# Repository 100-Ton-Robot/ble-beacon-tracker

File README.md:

# BLE Beacon Tracker (DIY)

A passive BLE beacon locator. Three Seeed XIAO nRF54L15 scanners sit behind directional antennas
facing out 120 deg apart. Comparing RSSI between sectors gives a bearing, and RSSI gives a rough
range. An ESP32-S3 Ethernet gateway (ESPHome) collects the scanners' data and publishes it to MQTT
for a tracker in Home Assistant.

Passive RSSI only: it works with any beacon, with no pairing and no Channel Sounding.

## What's here

| Folder | What it is |
| --- | --- |
| [`scanner_fw/`](scanner_fw/README.md) | Scanner firmware: nRF Connect SDK / Zephyr behind MCUboot, with signed BLE updates. Build, flash, console commands; gateway protocol in `scanner_fw/PROTOCOL.md`. |
| [`gateway/`](gateway/README.md) | ESPHome package, per-mast example config and the `sector_scanner` external component: protocol 3 buckets in, MQTT layout v3 out (batched RSSI, Theengs-style adverts, status, events, security stream, retained scanner state); the RX pin is the sector; watches each sector's chip ID, checks each scanner's firmware version and its input, drops the mast's ignore list, keeps the scanners' settings applied and passes commands to them. |
| `builds/` | The mast's shield deck, faces and end plate, two ways: the PCB build ([`builds/pcb/`](builds/pcb/README.md): Gerbers and a 1:1 print; build guide [`BUILD.md`](builds/pcb/BUILD.md)) and the hand build ([`builds/hand/`](builds/hand/README.md): printable 1:1 templates; build guide [`BUILD.md`](builds/hand/BUILD.md)). Each has its own `parameters.csv`. |
| [`boards/`](boards/README.md) | Module boards either build can use: the one-radio carrier (Up + two branch ports), a three-radio board and the LED add-on board (not designed in the repo yet), plus `lib/kicad_lib.py`, the KiCad helpers every board generator shares. |
| [`common/`](common/) | What both builds share: `parameters.csv` (faces and core, duck spacing, pipe, radio positions, enclosure, RF), `params.py` (loads common + one build's file) and `layout.py` (the derived layout both builds and the RF model use). |
| [`sim/`](sim/README.md) | ngspice models of the unified power + LED board (5 V rail, level-shifted data, boot pull-down, strip short) and a model of the LED direction ring. Values from `parameters.csv` files. |
| [`rf_model/`](rf_model/README.md) | openEMS (FDTD) model of one sector: deck, core and whips from the `parameters.csv` files (`--build pcb` or `hand`); gives the antenna pattern, match and isolation between sectors. Runs in Docker. |
| [`docs/ANTENNA_SELECTION.md`](docs/ANTENNA_SELECTION.md) | Which antenna and duck spacing to use, with the formulas and the RF results behind it. Generated by `docs/make_antenna_doc.py` from `parameters.csv` and the RF runs. |
| [`experiments/`](experiments/kicad_deck/README.md) | Side experiments (the deck redone in KiCad). |

Changes are listed in [`CHANGELOG.md`](CHANGELOG.md). How to report a vulnerability, and the
known security gaps that were reviewed and accepted (with the reasons), are in
[`SECURITY.md`](SECURITY.md). Prebuilt scanner update images are in
`scanner_fw/release/`. They only install on scanners whose
MCUboot was built with the same signing key, so build your own from source with your own key
(see `scanner_fw/README.md`).

## Status

Work in progress:
- Scanner firmware 0.7.0 (protocol 3) runs on three boards, checked over the USB console.
  0.8.0 (gateway TX moved from D6 to D8) is built but won't be flashed: D8 has no UART on the
  nRF54L15, so it can't carry the stream. Both builds are now drawn for relay protocol 4 star
  wiring (D10 uplink, D7 command RX, head D0 / D1 branch RX; see
  [Firmware and pins](builds/hand/README.md#firmware-and-pins-both-builds)). That firmware isn't written yet.
- The gateway (protocol 3, needs scanner firmware 0.5.0 or later) passes its boot self-test on
  a board, but hasn't received scanner data on real wiring yet.
- The Home Assistant tracker isn't written yet.

## Bugs and contributions

Bug reports and pull requests are welcome: use [Issues](../../issues). For firmware problems,
include the version, the console's `status` output and what you expected to happen.

## License

[MIT](LICENSE).

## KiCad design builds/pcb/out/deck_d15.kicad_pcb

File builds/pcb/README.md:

# Deck, face and end plate PCBs (parts on the deck)

The PCB build. The hand build of the same mast is in [`../hand/README.md`](../hand/README.md); both share [`common/parameters.csv`](../../common/parameters.csv) and [`common/layout.py`](../../common/layout.py). This build's own numbers (tracks, clearances, part positions, face tabs, end plate) are in [`parameters.csv`](parameters.csv) here.

Five boards, generated with KiCad from [`make_pcbs.py`](make_pcbs.py): two deck sizes (one per duck spacing), the face, the corner gusset and the optional end plate. **To build one, follow [`BUILD.md`](BUILD.md)**: decisions, boards to order with fab settings, BOM, the 1:1 print check and the assembly steps (generated from the CSVs here by `docs/make_build_docs.py`). This README describes the boards and how to regenerate them.

This build replaces the hand-drilled acrylic electronics plate, the bus board / unified stripboard and the hand-cut copper-clad faces. The older deck (`../hand/shield_deck_gerbers.zip`, 146 mm, no parts) and the plate templates stay in [`../hand/`](../hand/README.md) for the older build. Status: **generated and DRC-clean, not yet ordered or built** (revision 3, 2026-11-23; spec [`REV3_PLAN.md`](REV3_PLAN.md)). Preview: [`pcb_preview.png`](pcb_preview.png).

> **Unplug PoE before plugging in USB.** All modules share one 5 V rail, with no diodes. Plugging a USB cable into a XIAO or the ESP32 while the PoE splitter is feeding the deck ties the computer's USB VBUS to the splitter's 5 V. Power from PoE OR from USB, never both. Damage to the boards, the splitter or the computer from ignoring this is not covered by anything in this repo; you build and power it at your own risk. The same warning is on the deck, on each face and on the end plate, and "UNPLUG POE / BEFORE USB" sits right in front of each XIAO's USB-C plug (across the plug path) and beside J2 (both sides). Every warning has a drawn caution sign (triangle with !, ISO 7010 W001 style; the silkscreen font has no emoji).

> **Firmware:** this deck wires the radios for relay protocol 4 (star wiring: D10 uplink TX, D0 / D1 branch RX, D7 command RX). That firmware is not written yet; scanner firmware 0.8.0 and older (one TX per radio straight to the gateway) does not work on this deck. See [Firmware and pins](#firmware-and-pins-both-builds).

## Firmware and pins (both builds)

Both builds run the same scanner firmware ([`scanner_fw/`](../../scanner_fw/README.md)), but today the pins don't agree:

| | Uplink TX (to the gateway or the head radio) | Command RX | Branch RX |
| --- | --- | --- | --- |
| Hand build, templates page 6 (2026-11-24, relay protocol 4) | D10 (head S0 to the ESP32, S1 / S2 to the head) | D7 | head D0 (S1) / D1 (S2) |
| Hand build, masts wired before 2026-11-24 | D6 (issue #1's move to D8 is cancelled) | D7 | - |
| Scanner firmware 0.8.0 (`scanner_fw/app.overlay`) | D8 | D7 | - |
| PCB deck rev 3 (relay protocol 4) | D10 (head to J1 DATA, the other two to the head) | D7 | head D0 / D1 |

D8 has no UART on the nRF54L15, so the D8 wiring of issue #1 and firmware 0.8.0 can't carry the stream. Both builds are now drawn on the protocol 4 pins (D10, D7, D0 / D1), the one firmware for both; it isn't in `scanner_fw/` yet (0.8.0 is still per-radio D8).

## Deck

Revision 3 puts the three radios inside the triangle core, so every net runs inside the shield. The two deck files differ only in the diameter and the D hole positions.

- **Top (electronics side):** bare board except the parts, the +5 V tracks (0.8 mm), the signal stubs to the XIAO pads and the GND rim ring. **Bottom (antenna side):** solid GND, the shield. Inside the core (behind the reflectors, `CORE_MARGIN` 1 mm clear of the seam strip) both layers carry signals: the CMD ring and spokes, the two branch lanes along faces S0 and S2, the head's DATA track to J1, and the J1 / J2 pins. Outside the core the bottom copper is unbroken.
- **Rules:** a custom DRC rule (`out/*.kicad_dru`, written by the generator) keeps +5 V copper at least 0.5 mm from every other net (0.2 mm elsewhere). The bottom GND pour is held 2 mm back from every +5 V pad, inside the core only, so the seam strip stays whole.
- **Size:** diameter = larger of 144 mm (face corners at r 69.3 + 2.7 mm, as the end plate) and 2 x (inradius + duck spacing + 6 mm pad + 1.5 mm edge margin): 144 mm at 15 mm, 146.3 mm at 31 mm.
- **Holes:** D, P, P2 RP-SMA holes (6.5 mm, plated, 12 mm exposed GND pads both sides). One antenna per sector: D, P or P2 ("ONE ANTENNA: D, P OR P2" on the bottom). At 15 mm the D and P pads overlap; they are the same GND net and merge (holes 1.5 mm apart). A centre knockout, the same as the end plate's: a 2 mm routed ring (outer edge 22.2 mm, 7/8 in) held by four 5 mm bridges with six 0.5 mm mouse-bite holes each on the plate side (sizes below, under Fab rules), around a disc with a 6.5 mm RP-SMA hole (its own copper, net GND_KO). On a deck, break it out and file the nubs to pass the 1/2 in PVC pipe adapter (21.3 mm OD); no wires pass through the deck, Ethernet runs inside the pipe. Three M3 holes (3.4 mm, plated, 7 mm GND ring both sides) at r 25.75 mm, 342 / 102 / 222 deg, in the free ring between the radios: they register the deck to the collar, with a 10 mm washer keep-out marked on both sides (no tracks or vias in it). The 62 mm opening and the bayonet lugs are gone.
- **Exposed copper:** 4 mm rim ring both sides (36 stitching vias in it), the 6 mm seam strip under the faces on the bottom, the RP-SMA pads, the M3 rings, the M4 service-bolt pads.
- **Centre clearance:** nothing tall within 39.4 mm across the centre on either side (`DECK_CENTRE_CLEAR` 39 mm, checked by the generator), for a 1/2 in PVC pipe or a threaded 1/2 in fitting and its nut (about 34 mm across the corners, an estimate: measure yours). Only flat copper is inside it: the +5 V ring (top), the CMD ring (bottom) and the tracks into them. The tie squares set the limit; past them the M3 washers start at 41.4 mm.
- **Service bolts (M4, 2026-11-23):** a 5.2 mm plated hole (`M4_PLATE_HOLE`, oversize for play) with a 9 mm bare GND pad both sides at each core corner, 58.1 mm out on the corner axis (`r_M4` in `common/layout.py`: an M4 nut with its flats `NUT_GAP` 0.5 mm off both faces' inner sides), on the deck and the end plate. Each bolt goes into an M4 nut on a corner gusset (see Gusset); M4 x 14 cap bolt with a washer: plate 1.6 + 5.0 mm gap + gusset 1.6 + nut 3.2 + washer 0.8 leaves a thread or two past the nut. Snug them (0.5-1 N.m); the bolts pull the plate onto the face edges, and a plate comes off with three bolts. On the deck the bolt head sits right in front of each XIAO's USB-C plug path on purpose: USB is for bench flashing and recovery, with the bolt out.
- **Face slots:** three 2.0 x 9.4 mm milled slots per face along the seam lines (at the face centre and 17 mm either side), centred on the face board. A 2.0 mm slot has R 1.0 ends, so an 8.0 x 1.6 mm tab needs at least 8.8 mm; 9.4 mm keeps 0.2 mm at +-0.2 mm fab tolerance on tab and slot and leaves +-0.3 mm of slide. Top copper is kept 1 mm clear of every slot.
- **XIAOs (U2-U4):** one per core corner (60 / 180 / 300 deg), on the corner axis, USB-C end out toward the corner, antenna end in: antenna end 24 mm from the centre, centre 34.5 mm, USB-C end 45 mm. All castellated pads (lengthened for an iron) are inside the core; their outer corners are 1.0 mm from the seam strip, right on the 1 mm margin. The USB-C plug path (13 x 25 mm past the USB-C end, drawn on the print) runs out over the corner, clear of every antenna pad; the M4 service bolt blocks it while fitted (see Service bolts). The corner labels ("U2 HEAD", "U3 -> HEAD D0", "U4 -> HEAD D1") sit past the bolt's washer pad. Each radio feeds the sector 60 deg counter-clockwise of it: U2 (2 o'clock) -> S0, U3 (6 o'clock) -> S1, U4 (10 o'clock) -> S2.
- **Wiring (star, relay protocol 4):** U2 is the head. U2 D10 (uplink TX) -> J1 DATA. U3 D10 -> U2 D0 (Branch 1); U4 D10 -> U2 D1 (Branch 2). J1 CMD -> every D7. Every 5V pad runs to the +5 V ring round the pipe hole, and J1 and J2 feed the ring. Each XIAO's GND pad goes by a via to the bottom shield. The other pads are solder for strength only.

| J1 pin | Net | Carrier Up port colour | ESP32-S3-ETH |
| --- | --- | --- | --- |
| 1 | 5V | red | 5V |
| 2 | GND | black | GND |
| 3 | DATA (head D10, uplink) | yellow | a gateway RX pin (GPIO17 = gateway pin 0) |
| 4 | CMD (every D7) | green | GPIO21 (command TX) |

- **J1:** JST B4B-PH-K-S (2.0 mm, vertical, through-hole), the same pinout as the XIAO carrier board's Up port, on the head's corner axis just inside its antenna end (pin row at r 22.2 mm, 60 deg, parallel to the XIAO's antenna-end edge). **Fit it on the bottom**, housing inside the core with its deep side toward the rim, so the top keeps only the pins (cut flush) and both sides stay clear round the centre. Seen from the top, pin 1 (square pad) is at the counter-clockwise end. Moved 2026-11-23 from r 17 mm, 76 deg on the top.
- **J2 (5V in from the splitter):** a JST PH 2-pin footprint (B2B-PH-K-S), pin 1 = +5 V, pin 2 = GND, on U4's corner axis just inside its antenna end (pin row at r 22.2 mm, 300 deg, parallel to that edge), fitted on the bottom like J1 (moved 2026-11-23 from r 17.5 mm, 322 deg). Fit a B2B-PH-K-S and crimp the splitter lead, or solder the lead straight into the holes (0.75 mm drill, up to about 24 AWG).
- **Antenna strain relief ties:** three 12.5 mm squares ("ANT STRAIN RELIEF TIE"), one per XIAO pigtail, for 1/2 in HS-100 adhesive tie mounts (mask only underneath). Each pigtail leaves its IPEX4 at 248 deg in the corner frame (68 deg off straight in, toward its own sector; 236 until 2026-11-23, turned to take the squares out of the centre clearance); the square sits 15 mm along it (centre r 27.3 mm), turned so two sides are square to the straight line from the IPEX4 centre (the generator asserts this). A dotted line runs from the IPEX4 marker along the pigtail through the square, then bends about 30 deg toward its sector's D, P or P2 hole and ends in an arrow before the face slots. Clearances, checked by the generator (KiCad's DRC can't see silkscreen-only footprints): 8.6 mm from the 22.2 mm hole edge, 1.4 mm from the nearest face slot, 2.5 mm from the nearest pad or M3 washer keep-out; inner edge 19.7 mm from the centre.
- **C1 (bulk capacitor): not on this revision.** The 8 mm dual footprint (SMD 8 x 10 or radial, 11 x 9.2 mm courtyard) has no clear spot inside the core. A search of the routed board found room for an 8 mm radial can only near the 6 o'clock XIAO (r 19.5 mm, 194 deg, about 33 mm from J2), and for a 6.3 mm can about 7 mm from J2 (r 19 mm, 300 deg). Open: owner to choose.
- **Removed in revision 3:** the LED block (U1, R1, R2, C2, C3, F1, J3, J4) and every LED net (the LED board has its own connector to the ESP32), the service switch loop SW1 and its silkscreen, the back-feed diodes, R3, the collar arrows.
- **Heat near the seams:** there is no hard keep-out. The XIAO pads are 1.0 mm from the seam strip and 7.0 mm from the nearest slot; J1 and J2 are 16 mm away (`out/deck_d15_part_clearance.csv`). Soldering the faces first, on the bare boards, is what protects them.
- **Bottom silkscreen:** guide lines either side of the seam strip, a tick at each face's centre ("FACE Sn CENTRE"), "ONE ANTENNA: D, P OR P2" per sector, "SOLDER FACES BEFORE ANY PARTS", "THIS SIDE TO THE CORE (AS DECK OR END PLATE)", the duck spacing, the J1 / J2 outlines, the repo URL.
- **Repo URL:** `github.com/100-Ton-Robot/ble-beacon-tracker` is on every silkscreen: both sides of the deck, the face and the end plate.
- **Deck as end plate:** with 15 mm ducks the deck and the end plate are both 144 mm, so a second deck board turned over (bottom up, to the core) works as the end plate: its seam strip faces the faces, the slots are symmetric, and its knockout stays in for a downward antenna (or comes out for the pipe). The XIAO, J1 / J2 pads and +5 V tracks end up outside, unused and unpowered; "AS END PLATE: THIS SIDE OUT, NO PARTS" is on the top. The RF model gives the same result as the end plate PCB (`../../rf_model/README.md`). At 31 mm the deck is 146.3 mm, past the ~146 mm where the earlier simulation saw a plate start to block the ducks' downward view: use the end plate PCB there. The end plate PCB stays as the option for both.

## Face

Four corner-gusset slots, two near each end (see Gusset), with no stitching vias in or beside them. Solid GND both sides, one 6.5 mm plated RP-SMA hole at the centre (`DIPOLE_HOLE`) with a 12 mm exposed nut pad and four stitching vias round it, for an antenna on the face (a dipole or the printed fin); the nut sits on the inside, so keep modules inside the core clear of it (dropped and restored 2026-11-23). 3 mm of exposed copper along all four edges (seams to the other faces, the deck and the end plate), stitching vias. One design serves both plates: three 8 mm tabs on each end edge (centre and 17 mm either side), 1.6 mm long so they end flush with the deck's top and the end plate's outside, copper exposed for soldering into the slots. A router can't cut a sharp inside corner, so each tab root has a 2.2 x 1.2 mm relief notch on both sides: the bit's corner radius lands in the notch, and the edge that seats on the plate stays straight up to the tab. The notches end 23 mm from the face centre, well clear of the corners; the 2.2 mm gaps are far below a wavelength (~125 mm at 2.4 GHz) and the seam solder fills them. Tabs alone don't square a face (a 1.6 mm board in a 2.0 mm slot, 1.6 mm deep, can tilt up to ~19 deg), but held by both plates 120 mm apart the tilt is at most ~0.3 deg. Silkscreen: centre line, "OUTSIDE - DIPOLE SIDE" / "INSIDE - CORE SIDE", the tab marks at both ends and the power warning on the outside. No M2 posts and no other holes.

## Gusset

A small board in each core corner, parallel to the plates, that holds the M4 nut for a service bolt: 3 at the deck end and 3 at the end plate end. Its two side edges are full-length tabs (13.9 mm along the face) that pass through the face slots and stand 1 mm proud of the face's outer surface (`GUSSET_TAB_PROUD`), so they can be soldered inside and out. It runs from 51.5 to 63.5 mm out on the corner axis (`GUSSET_R`); the tip stops 2.6 mm short of the faces' inner corner, clear of the seam fillet. A 4.8 mm plated hole at r_M4 with the nut soldered on the side away from the plate; bare copper both sides (no mask), GND. Under bolt tension the gusset rides up to the slot edge nearest the plate: 5.0 mm from the plate's inner surface. Strength (hand calculation, FR-4): once the plate seats, the 5 mm strip of face between the end edge and the slot is in compression (several kN); as a beam before it seats it takes about 2.3 kN, and the two tab roots about 4 kN in shear, against about 1.2 kN from an M4 at 1 N.m. Outline also as `out/gusset_outline.dxf` for a 3D-printed or hand-cut gusset.

The face slots: four per face, 2.0 x 14.5 mm (the tab plus `GUSSET_SLOT_PLAY` 0.3 mm each end), centred `GUSSET_SLOT_DEPTH` 6 mm below each end edge (5-7 mm, clear of the 3 mm seam band), 40.1-54.6 mm off the face centre (5.4 mm in from the face end). With 10 mm tape on the inside seams, keep the face leg to 4.5 mm near the slots. The RF model's face copper shows the slots open (the tabs fill them in the build); at 2 x 14.5 mm against a ~125 mm wavelength that is expected to be negligible.

## End plate (optional)

A second shield plate across the far end of the triangle, `FACE_H` (120 mm) below the deck. The RF model (openEMS, 2026-11-22) gave median bearing error 20 -> 16 deg and better back rejection at steep downward angles with a 140 mm plate; 144 mm was chosen to leave 2.7 mm of plate past the face corners (r 69.3 mm) and is under the ~146 mm where the plate starts to reach past the ducks. 144 mm itself was not simulated.

- **Copper:** solid GND both sides with stitching vias, no parts. The 6 mm seam strip is exposed on the inside (top), where the faces solder on.
- **Face slots:** the same nine 2.0 x 9.4 mm slots as the deck, with the same guide lines and face centre ticks.
- **Service bolts:** the same three M4 holes as the deck, at the core corners, into the end-plate-end gussets (see Deck, Gusset).
- **Centre:** a 6.5 mm plated RP-SMA hole for a downward antenna, in a knockout. The knockout is a 2 mm routed ring (outer edge 22.2 mm, 7/8 in) held by four 5 mm bridges with six 0.5 mm mouse-bite holes each, on the plate side (sizes under Fab rules). Break it out (and file the nubs) to pass the 1/2 in PVC male adapter thread (21.3 mm OD). The disc is its own copper (net GND_KO), not tied to the plate once the ring is routed; an antenna in it is grounded through its coax.
- **Pigtail through the ring:** with the knockout kept in, an IPEX4 (MHF4) pigtail can pass through one of the four ring gaps (2.0 mm wide, ~10.9 mm long on the centreline with 5 mm bridges, curving only ~0.2 mm over a plug length). Feed the plug edge-on: its thickness (1.2 mm mated height max) goes across the gap. Flat, it is about as wide as the gap, so don't force it. 0.81 mm and 1.13 mm coax both pass. The plug's plan outline wasn't measured: hold a pigtail against the ring on the 1:1 print before relying on it. If it's tight, `KO_CHANNEL` (`parameters.csv`) can go to 2.5 mm, at some cost to bridge strength. Deburr the routed edges with a needle file, wrap two or three turns of Kapton tape round the coax where it sits in the gap (about 0.3 mm extra, it moves with the cable), keep the bend radius at 3.2 mm or more for 0.81 mm coax, and fix the cable in the gap with a dab of RTV silicone or hot glue so it can't saw back and forth. Heat-shrink won't go over a fitted plug.
- **Adapter:** the pipe glues into the adapter's socket from above, the adapter's shoulder sits on the plate inside the core, the thread goes down through the knockout and a 1/2 in IPS faucet mounting lock nut on the outside clamps the plate (mechanical only, no seal). A 54 mm keep-clear ring is marked on both sides (lock nut estimated at 50 mm across). Check on the dry fit that the assembly still comes out of the housing on the one post nut.
- **Silkscreen:** inside: "END PLATE - INSIDE", the build-order note; outside: the power warning, the knockout note. Revision 3 removed the service switch hole and its "RUN" / "SERVICE" marks.

## Ordering

Boards, quantities, fab settings and notes to the fab are in [`BUILD.md`](BUILD.md#boards-to-order), the BOM in [`BUILD.md`](BUILD.md#bill-of-materials-one-mast). The fab limits the boards are generated to are below.

## Fab rules

What the board house can make is a separate set of numbers from the design: [`../../fab/board_rules.csv`](../../fab/board_rules.csv) is the master (every `FAB_*` rule, set to the stricter of JLCPCB's and PCBWay's published 2-layer limits), and a file in [`../../fab/overrides/`](../../fab/overrides/) changes some of them for one fab (`jlcpcb.csv`, `pcbway.csv`) or for a builder's own requirements. An override may only change a rule the master has. To change a rule, change the CSV and regenerate; nothing is typed into the boards by hand.

The generator uses the rules three ways:

- **Checks the design against them** before drawing, and stops if a size is below a rule: `TRACK` >= `FAB_TRACK_MIN`, `CLEARANCE` >= `FAB_CLEARANCE_MIN`, `VIA` pad and drill and their annular ring, `EDGE_CLEAR`, `SLOT_W` and `KO_CHANNEL` >= `FAB_SLOT_NPTH_MIN`, the face fit (`SLOT_W` - `FAB_OUTLINE_TOL` >= `FACE_THICK` x (1 + `FAB_THICK_TOL`)) and the tab fit (`SLOT_L` >= `TAB_W` + slot-end sag + 2 x `FAB_OUTLINE_TOL`).
- **Sizes parts up to them:** knockout bridges are the larger of `KO_BRIDGE` and `FAB_BREAKAWAY_TAB_MIN` (5 mm), mouse bites the larger of `MOUSE_BITE` and `FAB_NPTH_MIN` (keeping the design's 0.25 mm web, as many as fit across the bridge), and every silkscreen line and text is at least `FAB_SILK_LINE_MIN` wide and `FAB_SILK_TEXT_MIN` high (library footprints included).
- **Holds DRC to them:** each board's design settings (minimum track, clearance, via, annular ring, drill, copper to edge, copper to hole `FAB_HOLE_CLEAR_MIN`, mask web, silk text) and its `.kicad_dru` (via drill, annular ring, hole to hole on different nets) come from the rule set, so a rule broken anywhere shows as a DRC error.

`out/` is built with the master rules; `out/fab_rules_used.csv` lists the set. With `--fab` / `--override` the boards go to `out_<name>/` (not committed), with their own `fab_rules_used.csv`.

## Rebuild

```
python3 make_pcbs.py                      # master fab rules, into out/
python3 make_pcbs.py --fab jlcpcb         # master + fab/overrides/jlcpcb.csv, into out_jlcpcb/
python3 make_pcbs.py --fab pcbway --override my_rules.csv   # then a builder's own rules, later files win
```

Needs KiCad 7 or later with its Python module (`pcbnew`) and `kicad-cli` on the path (on Debian / Ubuntu `apt install kicad kicad-footprints`), plus `pip install shapely pypdf pillow` (tie-mount clearance check, seam distance table, merged print PDF, preview) and `rsvg-convert` (preview). Sizes and rules come from `parameters.csv` here and `../../common/parameters.csv` (groups `pcb`, `face`, `endplate`, plus `deck` for the antenna hole geometry; `DECK_VARIANTS` lists the duck spacings built; `plate` for the XIAO size and `ADAPTER_HOLE` from `pipe`). Part positions and track routes are the tables in `make_pcbs.py`, in each corner's local frame: they are a layout, not measurements, so they live with the code.

Output in `out/`: `*.kicad_pcb` (open in KiCad 7+; KiCad 8 / 10 will upgrade the file on save), `*_gerbers.zip`, `*_drc.rpt`, `*.kicad_dru` (the +5 V clearance rule and the fab rules; keep it next to its board), `fab_rules_used.csv`, `deck_d*_part_clearance.csv`, `*_copper.json` (each board's copper as polygons plus its plated holes, for the RF model: `../../rf_model/sector_model.py --build pcb --deck d15 --copper`), and `../pcb_preview.png`. The DRC reports should show **0 errors**; the remaining warnings are silkscreen clipped by the exposed copper, "library not in configuration" for the generated footprints, and on the end plate "isolated copper fill" (its GND pour has no pads, only vias).

Routing is by hand in the script (no autorouter). If you move a part, re-run and read the DRC report: clearances, unconnected nets and courtyard overlaps are all checked there.

## Check a 1:1 print before ordering

`out/pcb_print_1to1.pdf` has the boards at 1:1 and the design formulas page with the radio placement (`common/formulas_page.py`). The checklist is in [`BUILD.md`](BUILD.md#before-ordering-check-a-11-print).

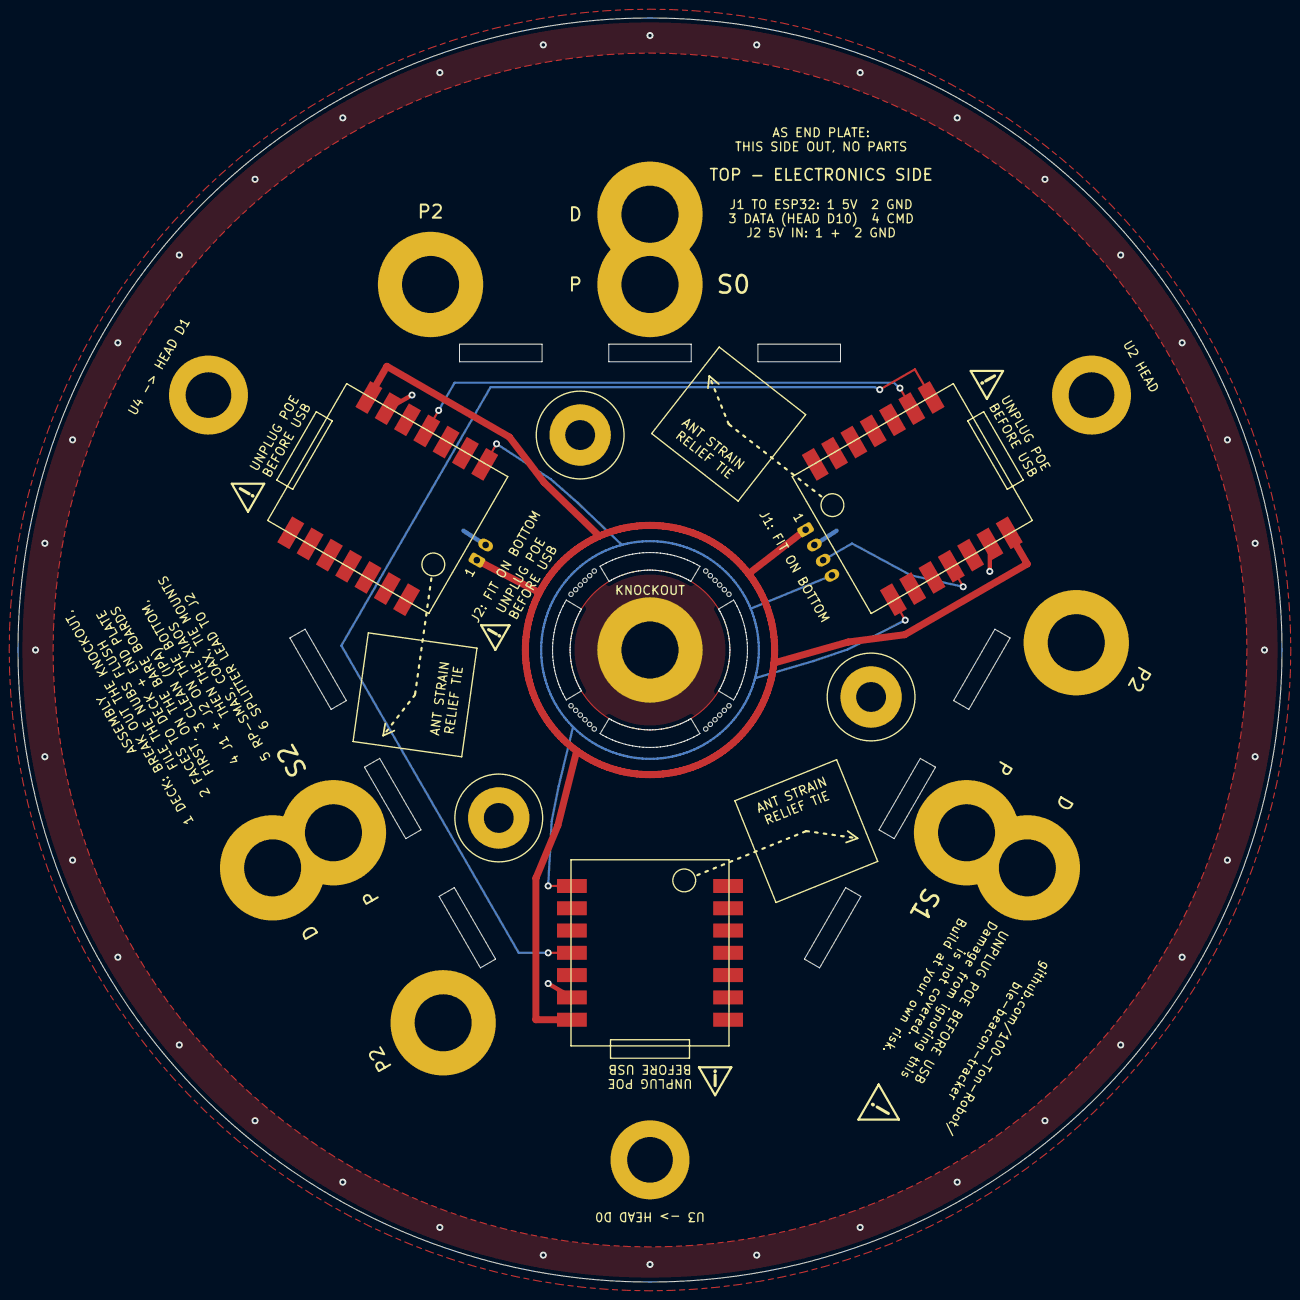
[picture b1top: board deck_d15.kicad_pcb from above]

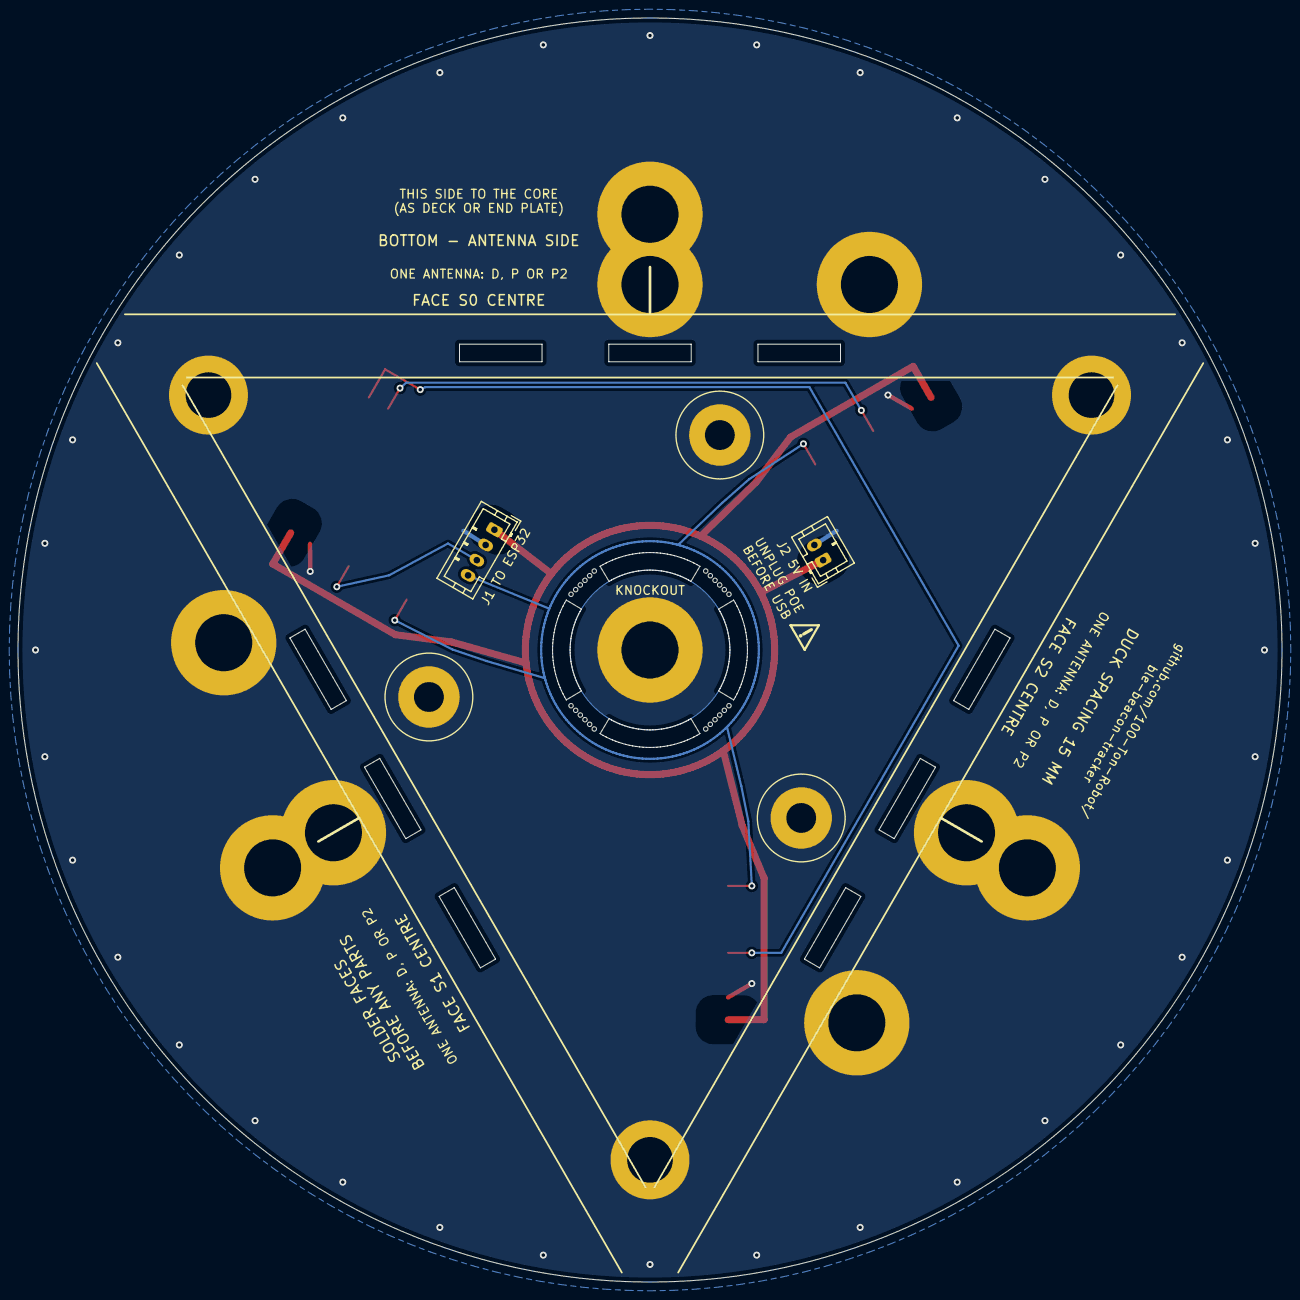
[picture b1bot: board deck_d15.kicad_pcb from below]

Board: 2 copper layers, 144.0 x 144.0 mm, 48 parts (2 on the bottom side), 6 nets.

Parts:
H1, H2, H3, H4, H5, H6, H7, H8, H9, H10: RP-SMA
J1: B4B-PH-K-S; JST_PH_B4B-PH-K_1x04_P2.00mm_Vertical
J2: B2B-PH-K-S; JST_PH_B2B-PH-K_1x02_P2.00mm_Vertical
M1, M2, M3: M3
M4, M5, M6: M4
MB1, MB2, MB3, MB4, MB5, MB6, MB7, MB8, MB9, MB10, MB11, MB12, MB13, MB14, MB15, MB16, MB17, MB18, MB19, MB20, MB21, MB22, MB23, MB24: hole
TM1, TM2, TM3: tie mount
U2, U3, U4: XIAO

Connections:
+5V: J1.1, J2.1, U2.5V, U3.5V, U4.5V
BRANCH1: U2.D0, U3.D10
BRANCH2: U2.D1, U4.D10
CMD: J1.4, U2.D7, U3.D7, U4.D7
DATA: J1.3, U2.D10
GND: H1.1, H2.1, H3.1, H4.1, H5.1, H6.1, H7.1, H8.1, H9.1, J1.2, J2.2, M1.1, M2.1, M3.1, M4.1, M5.1, M6.1, U2.GND, U3.GND, U4.GND

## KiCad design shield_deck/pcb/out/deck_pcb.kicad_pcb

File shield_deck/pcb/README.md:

# Deck, face and end plate PCBs (parts on the deck)

Four boards for PCBWay (or any fab), generated with KiCad from [`make_pcbs.py`](make_pcbs.py). The deck comes in two sizes, one per duck spacing (the D hole's distance in front of each face); order the one that matches your antennas:

| Board | File to upload | Qty per mast | Order |
| --- | --- | --- | --- |
| Deck, 15 mm ducks, 144 mm round: the shield plate the antennas go through, with the three scanners on top | `out/deck_d15_gerbers.zip` | 1 (this or the next) | 5 (minimum) |
| Deck, 31 mm ducks, 146.3 mm round: the same deck with the D holes 31 mm off the faces | `out/deck_d31_gerbers.zip` | 1 (this or the previous) | 5 (minimum) |
| Face, 120 x 120 mm (+ tabs): one side of the triangle reflector core | `out/face_pcb_gerbers.zip` | 3 | 5 (minimum), so order 5 per mast and keep 2 spare, or 10 for 3 masts |
| End plate, 144 mm round, optional: a second shield plate across the far end of the triangle. With 15 mm ducks a second deck board turned over does the same job (see Deck as end plate) | `out/endplate_pcb_gerbers.zip` | 0 or 1 | 5 (minimum) |

This build replaces the hand-drilled acrylic electronics plate, the bus board / unified stripboard and the hand-cut copper-clad faces. The older deck (`../shield_deck_gerbers.zip`, 146 mm, no parts) and the plate templates stay in `..` for the older build. Status: **generated and DRC-clean, not yet ordered or built** (revision 3, 2026-11-23; spec [`REV3_PLAN.md`](REV3_PLAN.md)). Preview: [`pcb_preview.png`](pcb_preview.png).

> **Unplug PoE before plugging in USB.** All modules share one 5 V rail, with no diodes. Plugging a USB cable into a XIAO or the ESP32 while the PoE splitter is feeding the deck ties the computer's USB VBUS to the splitter's 5 V. Power from PoE OR from USB, never both. Damage to the boards, the splitter or the computer from ignoring this is not covered by anything in this repo; you build and power it at your own risk. The same warning is on the deck, on each face and on the end plate, and "UNPLUG POE / BEFORE USB" sits right in front of each XIAO's USB-C plug (across the plug path) and beside J2 (both sides). Every warning has a drawn caution sign (triangle with !, ISO 7010 W001 style; the silkscreen font has no emoji).

> **Firmware:** this deck wires the radios for relay protocol 4 (star wiring: D10 uplink TX, D0 / D1 branch RX, D7 command RX). That firmware is not written yet; scanner firmware 0.8.0 and older (one TX per radio straight to the gateway) does not work on this deck.

## Build order

The deck's silkscreen carries the same list.

1. Deck: break out the centre knockout and file the bridge nubs flush, so the pipe adapter passes. (A deck board used as the end plate keeps its knockout unless the pipe goes through.)
2. Faces to the deck and the end plate first, on the bare boards: drop all three faces' tabs into the deck slots and the end plate slots together (dry fit), tack, check, then solder the seams. With both plates fitted no squareness jig is needed (see Face). Without the end plate, square the faces by eye or with a printed jig.
3. Clean (IPA).
4. J1 and J2 (either side, see Deck), then the XIAOs.
5. RP-SMAs, coax, antenna strain relief ties.
6. Splitter lead to J2.

To rework a seam later, remove the XIAOs first: their outer pad corners are 1.0 mm from the seam strip (`out/deck_d15_part_clearance.csv`).

## Deck

Revision 3 puts the three radios inside the triangle core, so every net runs inside the shield. The two deck files differ only in the diameter and the D hole positions.

- **Top (electronics side):** bare board except the parts, the +5 V tracks (0.8 mm), the signal stubs to the XIAO pads and the GND rim ring. **Bottom (antenna side):** solid GND, the shield. Inside the core (behind the reflectors, `CORE_MARGIN` 1 mm clear of the seam strip) both layers carry signals: the CMD ring and spokes, the two branch lanes along faces S0 and S2, the head's DATA track to J1, and the J1 / J2 pins. Outside the core the bottom copper is unbroken.
- **Rules:** a custom DRC rule (`out/*.kicad_dru`, written by the generator) keeps +5 V copper at least 0.5 mm from every other net (0.2 mm elsewhere). The bottom GND pour is held 2 mm back from every +5 V pad, inside the core only, so the seam strip stays whole.
- **Size:** diameter = larger of 144 mm (face corners at r 69.3 + 2.7 mm, as the end plate) and 2 x (inradius + duck spacing + 6 mm pad + 1.5 mm edge margin): 144 mm at 15 mm, 146.3 mm at 31 mm.
- **Holes:** D, P, P2 RP-SMA holes (6.5 mm, plated, 12 mm exposed GND pads both sides). One antenna per sector: D, P or P2 ("ONE ANTENNA: D, P OR P2" on the bottom). At 15 mm the D and P pads overlap; they are the same GND net and merge (holes 1.5 mm apart). A centre knockout, the same as the end plate's: a 2 mm routed ring (outer edge 22.2 mm, 7/8 in) held by four 2.5 mm bridges with three 0.5 mm mouse-bite holes each on the plate side, around a disc with a 6.5 mm RP-SMA hole (its own copper, net GND_KO). On a deck, break it out and file the nubs to pass the 1/2 in PVC pipe adapter (21.3 mm OD); no wires pass through the deck, Ethernet runs inside the pipe. Three M3 holes (3.4 mm, plated, 7 mm GND ring both sides) at r 25.75 mm, 342 / 102 / 222 deg, in the free ring between the radios: they register the deck to the collar, with a 10 mm washer keep-out marked on both sides (no tracks or vias in it). The 62 mm opening and the bayonet lugs are gone.
- **Exposed copper:** 4 mm rim ring both sides (36 stitching vias in it), the 6 mm seam strip under the faces on the bottom, the RP-SMA pads, the M3 rings.
- **Face slots:** three 2.0 x 9.4 mm milled slots per face along the seam lines (at the face centre and 17 mm either side), centred on the face board. A 2.0 mm slot has R 1.0 ends, so an 8.0 x 1.6 mm tab needs at least 8.8 mm; 9.4 mm keeps 0.2 mm at +-0.2 mm fab tolerance on tab and slot and leaves +-0.3 mm of slide. Top copper is kept 1 mm clear of every slot.
- **XIAOs (U2-U4):** one per core corner (60 / 180 / 300 deg), on the corner axis, USB-C end out toward the corner, antenna end in: antenna end 24 mm from the centre, centre 34.5 mm, USB-C end 45 mm. All castellated pads (lengthened for an iron) are inside the core; their outer corners are 1.0 mm from the seam strip, right on the 1 mm margin. The USB-C plug path (13 x 25 mm past the USB-C end, drawn on the print) runs out over the corner, clear of every antenna pad. Each radio feeds the sector 60 deg counter-clockwise of it: U2 (2 o'clock) -> S0, U3 (6 o'clock) -> S1, U4 (10 o'clock) -> S2.
- **Wiring (star, relay protocol 4):** U2 is the head. U2 D10 (uplink TX) -> J1 DATA. U3 D10 -> U2 D0 (Branch 1); U4 D10 -> U2 D1 (Branch 2). J1 CMD -> every D7. J1 and J2 5V -> every 5V pad. Each XIAO's GND pad goes by a via to the bottom shield. The other pads are solder for strength only.

| J1 pin | Net | Carrier Up port colour | ESP32-S3-ETH |
| --- | --- | --- | --- |
| 1 | 5V | red | 5V |
| 2 | GND | black | GND |
| 3 | DATA (head D10, uplink) | yellow | a gateway RX pin (GPIO17 = gateway pin 0) |
| 4 | CMD (every D7) | green | GPIO21 (command TX) |

- **J1:** JST B4B-PH-K-S (2.0 mm, vertical, through-hole), the same pinout as the XIAO carrier board's Up port, at r 17 mm, 76 deg, next to the head; pin row tangential, pin 1 (square pad) at the clockwise end. Its housing outline is printed on both sides: fit it on whichever side faces the ESP32.
- **J2 (5V in from the splitter):** a JST PH 2-pin footprint (B2B-PH-K-S), pin 1 = +5 V, pin 2 = GND, at r 17.5 mm, 322 deg, outline on both sides. Fit a B2B-PH-K-S and crimp the splitter lead, or solder the lead straight into the holes (0.75 mm drill, up to about 24 AWG).
- **Antenna strain relief ties:** three 12.5 mm squares ("ANT STRAIN RELIEF TIE"), one per XIAO pigtail, for 1/2 in HS-100 adhesive tie mounts (mask only underneath). Each pigtail leaves its IPEX4 at 236 deg in the corner frame (56 deg off straight in, toward its own sector); the square sits 15 mm along it (r 24.2 mm; 13 in the spec, moved out so it sits 3.3 mm clear of the XIAO and stays visible once the XIAO is on), turned so two sides are square to the cable. A dotted line runs from the IPEX4 marker along the pigtail through the square, then bends about 30 deg toward its sector's D, P or P2 hole and ends in an arrow before the face slots. Clearances, checked by the generator (KiCad's DRC can't see silkscreen-only footprints): 6.6 mm from the 22.2 mm hole edge (7.0 mm from the 21.3 mm pipe), 1.4 mm from the nearest face slot, 3.1 mm from the M3 washer keep-out, 2.2 mm from the nearest pad.
- **C1 (bulk capacitor): not on this revision.** The 8 mm dual footprint (SMD 8 x 10 or radial, 11 x 9.2 mm courtyard) has no clear spot inside the core. A search of the routed board found room for an 8 mm radial can only near the 6 o'clock XIAO (r 19.5 mm, 194 deg, about 33 mm from J2), and for a 6.3 mm can about 7 mm from J2 (r 19 mm, 300 deg). Open: owner to choose.
- **Removed in revision 3:** the LED block (U1, R1, R2, C2, C3, F1, J3, J4) and every LED net (the LED board has its own connector to the ESP32), the service switch loop SW1 and its silkscreen, the back-feed diodes, R3, the collar arrows.
- **Heat near the seams:** there is no hard keep-out. The XIAO pads are 1.0 mm from the seam strip and 7.0 mm from the nearest slot; J1 and J2 are 16 mm away (`out/deck_d15_part_clearance.csv`). Soldering the faces first, on the bare boards, is what protects them.
- **Bottom silkscreen:** guide lines either side of the seam strip, a tick at each face's centre ("FACE Sn CENTRE"), "ONE ANTENNA: D, P OR P2" per sector, "SOLDER FACES BEFORE ANY PARTS", "THIS SIDE TO THE CORE (AS DECK OR END PLATE)", the duck spacing, the J1 / J2 outlines, the repo URL.
- **Repo URL:** `github.com/100-Ton-Robot/ble-beacon-tracker` is on every silkscreen: both sides of the deck, the face and the end plate.
- **Deck as end plate:** with 15 mm ducks the deck and the end plate are both 144 mm, so a second deck board turned over (bottom up, to the core) works as the end plate: its seam strip faces the faces, the slots are symmetric, and its knockout stays in for a downward antenna (or comes out for the pipe). The XIAO, J1 / J2 pads and +5 V tracks end up outside, unused and unpowered; "AS END PLATE: THIS SIDE OUT, NO PARTS" is on the top. The RF model gives the same result as the end plate PCB (`../../rf_model/README.md`). At 31 mm the deck is 146.3 mm, past the ~146 mm where the earlier simulation saw a plate start to block the ducks' downward view: use the end plate PCB there. The end plate PCB stays as the option for both.

## Face

Solid GND both sides with no holes (the face-centre dipole hole was dropped 2026-11-23: not worth it, and it would clash with modules mounted inside the core), 3 mm of exposed copper along all four edges (seams to the other faces, the deck and the end plate), stitching vias. One design serves both plates: three 8 mm tabs on each end edge (centre and 17 mm either side), 1.6 mm long so they end flush with the deck's top and the end plate's outside, copper exposed for soldering into the slots. A router can't cut a sharp inside corner, so each tab root has a 2.2 x 1.2 mm relief notch on both sides: the bit's corner radius lands in the notch, and the edge that seats on the plate stays straight up to the tab. The notches end 23 mm from the face centre, well clear of the corners; the 2.2 mm gaps are far below a wavelength (~125 mm at 2.4 GHz) and the seam solder fills them. Tabs alone don't square a face (a 1.6 mm board in a 2.0 mm slot, 1.6 mm deep, can tilt up to ~19 deg), but held by both plates 120 mm apart the tilt is at most ~0.3 deg. Silkscreen: centre line, "OUTSIDE" / "INSIDE - CORE SIDE", the tab marks at both ends and the power warning on the outside. No M2 posts and no antenna holes.

## End plate (optional)

A second shield plate across the far end of the triangle, `FACE_H` (120 mm) below the deck. The RF model (openEMS, 2026-11-22) gave median bearing error 20 -> 16 deg and better back rejection at steep downward angles with a 140 mm plate; 144 mm was chosen to leave 2.7 mm of plate past the face corners (r 69.3 mm) and is under the ~146 mm where the plate starts to reach past the ducks. 144 mm itself was not simulated.

- **Copper:** solid GND both sides with stitching vias, no parts. The 6 mm seam strip is exposed on the inside (top), where the faces solder on.
- **Face slots:** the same nine 2.0 x 9.4 mm slots as the deck, with the same guide lines and face centre ticks.
- **Centre:** a 6.5 mm plated RP-SMA hole for a downward antenna, in a knockout. The knockout is a 2 mm routed ring (outer edge 22.2 mm, 7/8 in) held by four 2.5 mm bridges with three 0.5 mm mouse-bite holes each, on the plate side. Break it out (and file the nubs) to pass the 1/2 in PVC male adapter thread (21.3 mm OD). The disc is its own copper (net GND_KO), not tied to the plate once the ring is routed; an antenna in it is grounded through its coax.
- **Adapter:** the pipe glues into the adapter's socket from above, the adapter's shoulder sits on the plate inside the core, the thread goes down through the knockout and a 1/2 in IPS faucet mounting lock nut on the outside clamps the plate (mechanical only, no seal). A 54 mm keep-clear ring is marked on both sides (lock nut estimated at 50 mm across). Check on the dry fit that the assembly still comes out of the housing on the one post nut.
- **Silkscreen:** inside: "END PLATE - INSIDE", the build-order note; outside: the power warning, the knockout note. Revision 3 removed the service switch hole and its "RUN" / "SERVICE" marks.

## BOM (one mast)

| Ref | Part | Package | Qty |
| --- | --- | --- | --- |
| U2-U4 | Seeed XIAO nRF54L15 | castellated | 3 |
| J1 | JST B4B-PH-K-S; mating PHR-4 housing + SPH-002T-P0.5S crimps (4-wire harness to the ESP32, as the carrier Up port) | 2.0 mm TH | 1 |
| J2 | JST B2B-PH-K-S; mating PHR-2 + crimps on the splitter lead (or solder the lead into the holes) | 2.0 mm TH | 0 or 1 |
| - | 1/2 in HS-100 adhesive tie mounts | - | 3 |
| - | Deck PCB (15 or 31 mm ducks) | - | 1 |
| - | Face PCB | - | 3 |
| - | End plate PCB, optional | - | 0 or 1 |
| - | 1/2 in IPS faucet mounting lock nut (with the end plate and the pipe through it) | - | 0 or 1 |

C1 (bulk capacitor) is not on revision 3; see Deck.

## Order settings (PCBWay)

Same as the old deck ([../PCBWAY.md](../PCBWAY.md)) except:

| Setting | Deck | Face | End plate |
| --- | --- | --- | --- |
| Size | 144 x 144 mm (15 mm ducks) or 146.3 x 146.3 mm (31 mm ducks), round (outline, the knockout ring and the nine face slots in Edge_Cuts) | 120 x 123.2 mm (with the tabs) | 144 x 144 mm, round |
| Silkscreen | White, **both sides** | White, both sides | White, both sides |
| Min hole | 0.4 mm (vias) | 0.4 mm | 0.4 mm (vias); 0.5 mm mouse bites |
| Note to fab | "Round board, nine 2.0 mm milled slots (non-plated) and a routed centre knockout ring with mouse-bite bridges (keep the bridges). Large copper pour on the bottom is intentional (RF shield)." | "Tabs on two edges. Solid copper both sides is intentional (RF reflector)." | "Round board, nine 2.0 mm milled slots and a routed knockout ring with mouse-bite bridges (keep the bridges). Solid copper both sides is intentional (RF shield)." |

1.6 mm FR-4, 2 layers, 1 oz, HASL lead-free or ENIG (exposed copper must take solder). Check each in PCBWay's Gerber viewer before paying.

## Rebuild

```
python3 make_pcbs.py
```

Needs KiCad 7 or later with its Python module (`pcbnew`) and `kicad-cli` on the path (on Debian / Ubuntu `apt install kicad kicad-footprints`), plus `pip install shapely pypdf pillow` (tie-mount clearance check, seam distance table, merged print PDF, preview) and `rsvg-convert` (preview). Sizes and rules come from `../parameters.csv` (groups `pcb`, `face`, `endplate`, plus `deck` for the antenna hole geometry; `DECK_VARIANTS` lists the duck spacings built; `plate` for the XIAO size and `ADAPTER_HOLE` from `pipe`). Part positions and track routes are the tables in `make_pcbs.py`, in each corner's local frame: they are a layout, not measurements, so they live with the code.

Output in `out/`: `*.kicad_pcb` (open in KiCad 7+; KiCad 8 / 10 will upgrade the file on save), `*_gerbers.zip`, `*_drc.rpt`, `*.kicad_dru` (the +5 V clearance rule; keep it next to its board), `deck_d*_part_clearance.csv`, `*_copper.json` (each board's copper as polygons plus its plated holes, for the RF model: `../../rf_model/sector_model.py --deck d15 --copper`), and `../pcb_preview.png`. The DRC reports should show **0 errors**; the remaining warnings are silkscreen clipped by the exposed copper, "library not in configuration" for the generated footprints, and on the end plate "isolated copper fill" (its GND pour has no pads, only vias).

Routing is by hand in the script (no autorouter). If you move a part, re-run and read the DRC report: clearances, unconnected nets and courtyard overlaps are all checked there.

## Check a 1:1 print before ordering

`out/pcb_print_1to1.pdf` has seven A4 landscape pages: 15 mm deck top and bottom (mirrored, as seen from below), 31 mm deck top and bottom, one face, end plate inside, end plate outside (mirrored). Pads and exposed copper print black, with silkscreen, outline and holes. Print at 100% ("Actual size", not "Fit to page") and measure both 100 mm scale bars on each page before trusting it. Then lay the real parts on it: the XIAOs (castellations on the pads, IPEX4 on its circle; the outer pad corners have no spare against the core margin), a USB-C plug in each drawn plug path, J1 and J2, the tie mounts on their squares with a pigtail run to its sector's holes, the RP-SMA connectors in their holes, the pipe adapter in the 22.2 mm hole, an M3 washer on each 10 mm circle and the adapter / lock nut in the end plate's knockout ring.

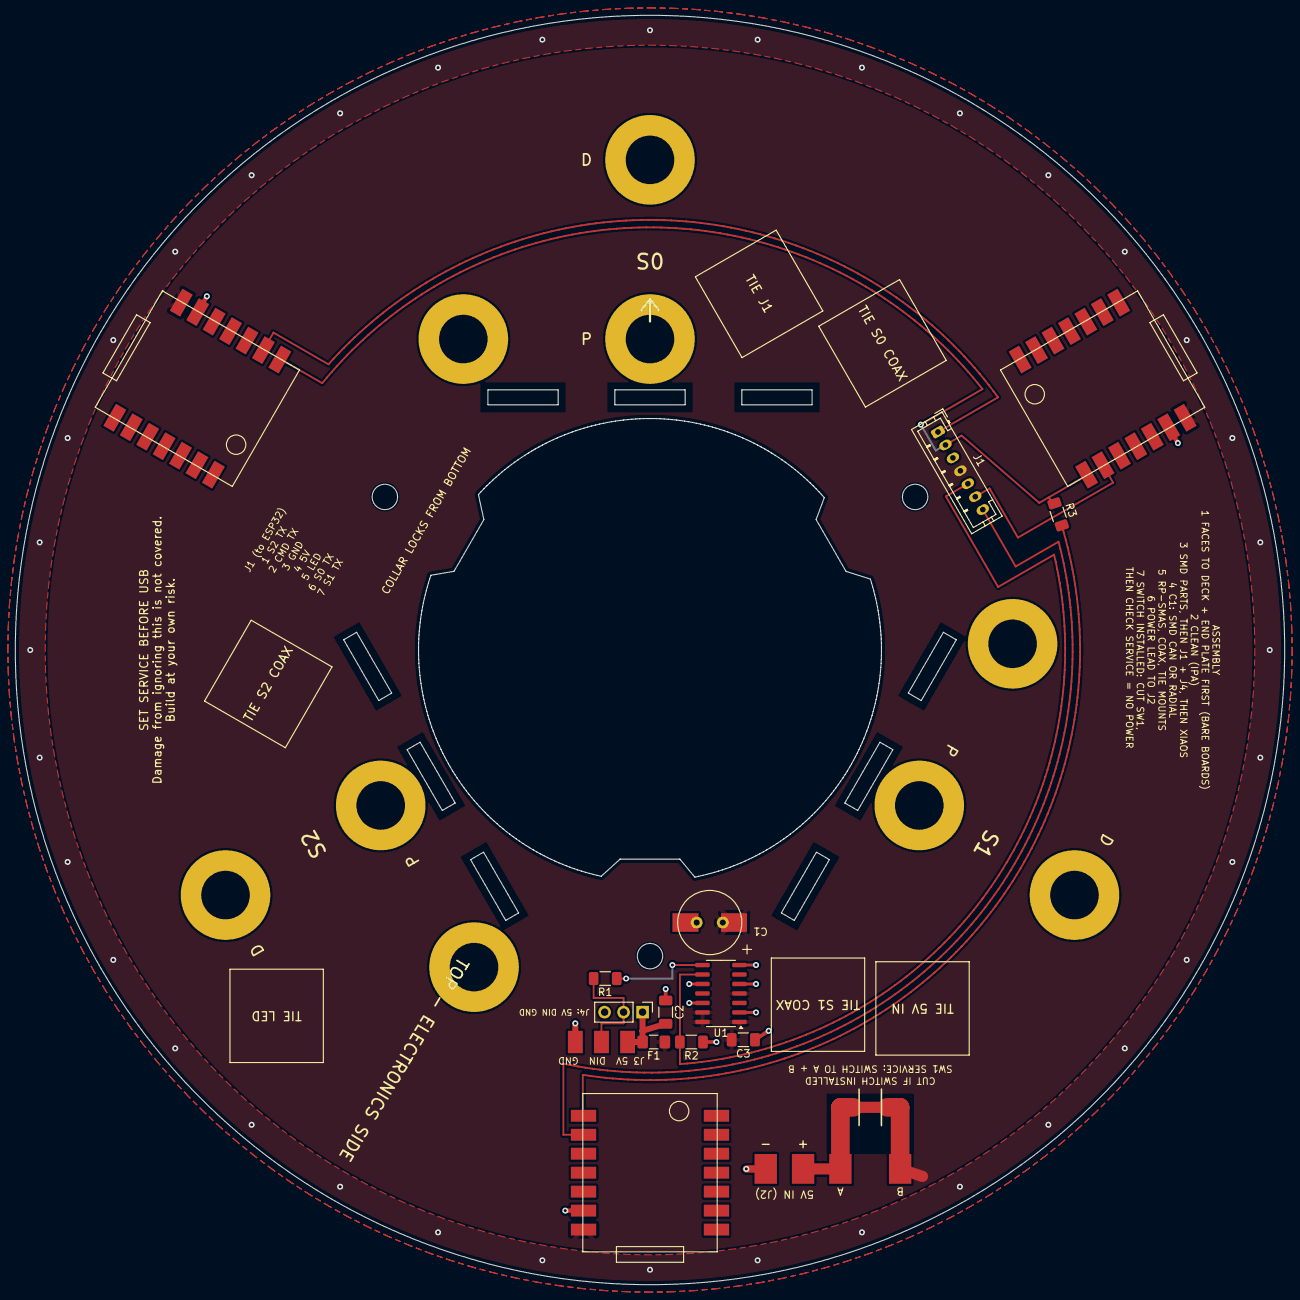
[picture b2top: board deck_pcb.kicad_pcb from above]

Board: 2 copper layers, 170.0 x 170.0 mm, 34 parts (0 on the bottom side), 12 nets.

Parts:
C1: 330u
C2, C3: 100n; C_1206_3216Metric_Pad1.33x1.80mm_HandSolder
F1: 2A one-time; Fuse_1206_3216Metric_Pad1.42x1.75mm_HandSolder
H1, H2, H3, H4, H5, H6, H7, H8, H9: RP-SMA
J1: B7B-PH-K-S; JST_PH_B7B-PH-K_1x07_P2.00mm_Vertical
J2: 5V IN
J3: LED strip
J4: 1x3 2.54 mm; PinHeader_1x03_P2.54mm_Vertical
M1, M2, M3: M3
R1: 330R; R_1206_3216Metric_Pad1.30x1.75mm_HandSolder
R2: 10k; R_1206_3216Metric_Pad1.30x1.75mm_HandSolder
R3: 0R jumper; R_1206_3216Metric_Pad1.30x1.75mm_HandSolder
SW1: loop / switch
TM1, TM2, TM3, TM4, TM5, TM6: tie mount
U1: 74HCT125; SOIC-14_3.9x8.7mm_P1.27mm
U2, U3, U4: XIAO

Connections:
5V_IN: J2.1, SW1.1
+5V: C1.1, C3.2, F1.1, J1.4, SW1.2, U1.1, U1.4, U1.13, U1.14, U2.5V, U3.5V, U4.5V
+5V_LED: C2.2, F1.2, J3.1, J4.1
BUF: R1.1, U1.8
CMD_TX: J1.2, R3.1, U2.D7, U4.D7
CMD_TX_S1: R3.2, U3.D7
DOUT: J3.2, J4.2, R1.2
GND: C1.2, C2.1, C3.1, H1.1, H2.1, H3.1, H4.1, H5.1, H6.1, H7.1, H8.1, H9.1, J1.3, J2.2, J3.3, J4.3, R2.1, U1.2, U1.5, U1.7, U1.10, U1.12, U2.GND, U3.GND, U4.GND
LED_IN: J1.5, R2.2, U1.9
S0_TX: J1.6, U2.D8
S1_TX: J1.7, U3.D8
S2_TX: J1.1, U4.D8

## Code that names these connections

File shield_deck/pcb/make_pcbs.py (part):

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        vg, v7, v10, v5 = GND_VIA_V, pin_v("D7"), pin_v("D10"), pin_v("5V")
        bd.track(L([(PIN_U, pin_v("GND")), (VIA_U, vg)]), "GND", 0.5)
        bd.via(loc(th, VIA_U, vg), "GND", VIA_D, VIA_DRILL)
        bd.track(L([(PIN_U, v7), (VIA_U, v7)]), "CMD", TRACK)
        bd.via(loc(th, VIA_U, v7), "CMD", VIA_D, VIA_DRILL)
        bd.track(L([(VIA_U, v7)] + SPOKE) + [circ(RING_CMD, SPOKE_END)], "CMD", TRACK, B)
        d10 = nets[th]["D10"]
        bd.track(L([(PIN_U, v10), (VIA_U, v10)]), d10, TRACK)
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            lane.append(circ(RING_5V, RING_5V_IN))
        bd.track(lane, "+5V", TRACK_5V)

    # J1 / J2: +5V pin straight in to the ring (top); J1 CMD straight in to its ring (bottom); GND pins out (bottom)
    for wp, r in ((w1["1"], RING_5V), (w2["1"], RING_5V)):
        bd.track([wp, pol(r, ang_of(wp))], "+5V", TRACK_5V)
    bd.track([w1["4"], pol(RING_CMD, ang_of(w1["4"]))], "CMD", TRACK, B)
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    ua = lambda d: (d - 0.5 * v10) / 0.866025  # noqa: E731     u (cw side) where the D10 row meets lane distance d
    # U4 -> head D1: outer lane on face 0
    bd.track([loc(t2, VIA_U, v10), loc(t2, ua(FACE_LANE_OUT), v10), s0(d1u - 0.7, FACE_LANE_OUT),
              loc(t0, *HEAD_D1_VIA)], "BRANCH2", TRACK, B)
    # U3 -> head D0: along face 240, under U4 (between its D7 and D10 vias), inner lane on face 0
    ub = (FACE_LANE_240 - 0.5 * UNDER_U4_V) / 0.866025
    uc = (FACE_LANE_IN - 0.5 * UNDER_U4_V) / 0.866025
    bd.track([loc(t1, VIA_U, v10), loc(t1, ua(FACE_LANE_240), v10), loc(t2, -ub, UNDER_U4_V),
              loc(t2, uc, UNDER_U4_V), s0(d0u - 0.6, FACE_LANE_IN), loc(t0, *HEAD_D0_VIA)], "BRANCH1", TRACK, B)
    for d in (FACE_LANE_IN, FACE_LANE_OUT, FACE_LANE_240):
        assert d + TRACK / 2 <= CORE_LIM, "branch lane outside the core"

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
